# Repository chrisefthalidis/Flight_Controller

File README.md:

This board is an embedded system based on the STM32F405RGT6 microcontroller. It incorporates an MPU9250 Inertial
Measurement Unit for attitude estimation, an SPL06-007 barometer for altitude estimation and a TESEO-LIV3F GNSS
receiver for position estimation. There is also a second Radio Transceiver board (based on the nRF24L01+ transceiver)
that is connected as a shield to the Flight Controller board. You will find all the necessary PCB design files from
Altium and KiCad inside the respective folders. The firmware is not fully finished yet, but you will find most of the
existing files inside the 'Firmware' folder, including ST's HAL drivers generated by STM32CubeMX, an SPL06-007
driver, an nRF24L01+ driver, a Complementary Filter implementation in C, a Kalman Filter implementation in C++, as well
as a PID Controller implementation in both C and C++. The MPU9250 driver, as well as the main.c function are coming
soon. The basic idea is that we read the values from all our sensors, we deploy some state estimation and sensor
fusion algorithms, and we use these states to control a quadcopter UAV. There is also an additional 'Radio Controller
(Ground Module)' board, that you will find on my GitHub page, which we can use to remotely control the quadcopter's
altitude using the on-board potentiometer.

P.S. These boards are not perfect in any way. They have some design mistakes, since they were 2 of my first boards.
I've learnt a lot since, and i keep getting better with each board that i design. If you have any questions, please
contact me at chrisefthalidis@gmail.com

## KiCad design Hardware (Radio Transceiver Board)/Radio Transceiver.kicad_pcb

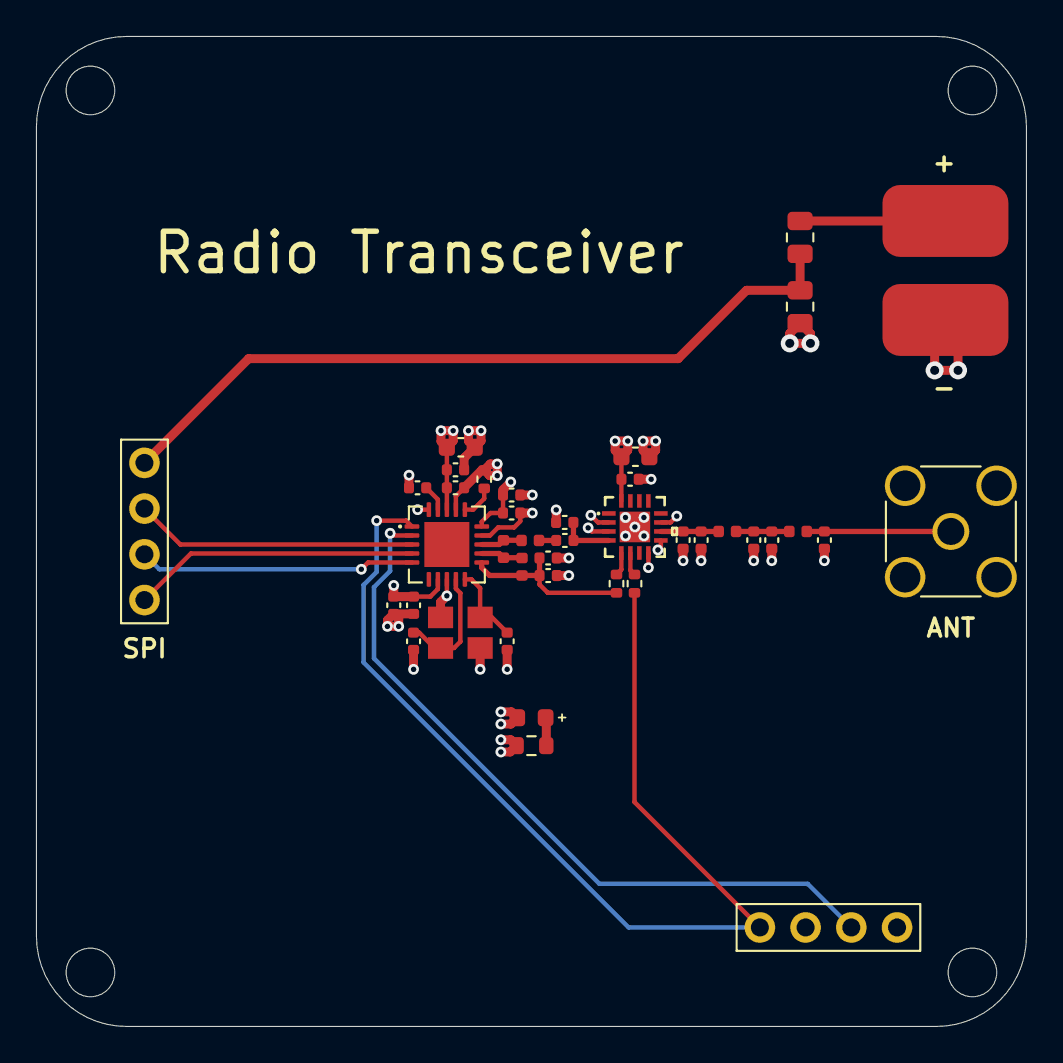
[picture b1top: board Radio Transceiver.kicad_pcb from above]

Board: 4 copper layers, 55.0 x 55.0 mm, 44 parts (0 on the bottom side), 24 nets.

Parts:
C1: 1uF; C_0603_1608Metric
C2: 220pF; C_0402_1005Metric
C3: 4.7uF; C_0603_1608Metric
C4, C6, C8: 10nF; C_0402_1005Metric
C5, C7, C9: 1nF; C_0402_1005Metric
C10: 4.7pF; C_0402_1005Metric
C11: 2.2nF; C_0402_1005Metric
C12, C18, C19, C20, C21: 1.5pF; C_0402_1005Metric
C13: 1pF; C_0402_1005Metric
C14: 33nF; C_0402_1005Metric
C15, C16: 12pF; C_0402_1005Metric
C17: 0.3pF; C_0402_1005Metric
D1: Green LED; LED_0603_1608Metric
H1, H2, H3, H4: MountingHole; MountingHole_2.7mm_M2.5
J1: KH-SMA-KE8-G; SMA_Amphenol_132291_Vertical
J2, J3: Conn_01x04; PinSocket_1x04_P2.54mm_Vertical
J4: Screw_Terminal_01x02; TerminalBlock_bornier-2_P5.08mm
L1: 2.7nH; L_0402_1005Metric
L2: 8.2nH; L_0402_1005Metric
L3: 3.9nH; L_0402_1005Metric
L4, L5: 2.4nH; L_0402_1005Metric
R1, R2: 1KΩ; R_0402_1005Metric
R3: 22ΚΩ; R_0402_1005Metric
R4: 33Ω; R_0603_1608Metric
R5: 30ΚΩ; R_0805_2012Metric
R6: 7.5ΚΩ; R_0805_2012Metric
U1: RFX2401C
U2: nRF24L01P; QFN-20-1EP_4x4mm_P0.5mm_EP2.5x2.5mm
Y1: X322516MLB4SI; Crystal_SMD_3225-4Pin_3.2x2.5mm

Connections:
+3V3: C1.1, C2.1, C3.1, C4.1, C5.1, C6.1, C7.1, C8.1, C9.1, J2.1, R4.1, U1.16, U2.7, U2.15, U2.18
+BATT: J4.1, R5.2
/ADC_IN: J3.4, R5.1, R6.2
/ANT: C17.1, C18.1, L4.2, U1.10
/ANT1: L1.2, L2.1, U2.12
/ANT2: L2.2, L3.2, U2.13
/CE: J2.4, R2.1, U2.1
/CSN: J2.2, U2.2
/MISO: J3.2, U2.5
/MOSI: J3.1, U2.4
/SCK: J3.3, U2.3
/TXRX: C12.1, C13.1, U1.4
/VDD_PA: C10.1, C11.1, L1.1, R1.1, U2.11
/XC1: C15.1, U2.10, Y1.1
/XC2: C16.1, U2.9, Y1.3
GND: C1.2, C2.2, C3.2, C4.2, C5.2, C6.2, C7.2, C8.2, C9.2, C10.2, C11.2, C13.2, C14.2, C15.2, C16.2, C17.2, C18.2, C19.2, C20.2, C21.2, D1.1, J1.2, J2.3, J4.2, R3.1, R6.1, U1.2, U1.3, U1.8, U1.9, U1.11, U1.17, U2.8, U2.14, U2.17, U2.20, Y1.2, Y1.4
unnamed: C12.2, L3.1
unnamed: C14.1, U2.19
unnamed: C19.1, C20.1, L4.1, L5.2
unnamed: C21.1, J1.1, L5.1
unnamed: D1.2, R4.2
unnamed: R1.2, U1.5
unnamed: R2.2, U1.6
unnamed: R3.2, U2.16

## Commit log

2021-11-06 Modify file
2021-11-06 Add file
2021-11-22 Add Complementary Filter
2021-11-22 Update Build directory
2021-11-22 Update Makefile
2021-11-22 Update settings.json file
2021-12-18 Modify variable type

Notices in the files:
parts and their libraries:
Copyright 2016 Accelerated Designs. All rights reserved.
